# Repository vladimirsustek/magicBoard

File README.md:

<h1>The magicBoard!</h1>

The magicBoard is supposed to multi-purpose embedded device based on the MCU ARM-M7<br> 
STM32F767ZI, namelly on the development board [STM32 Nucleo-144](https://www.st.com/en/evaluation-tools/nucleo-f767zi.html)
equipped with customized<br>shield to extend Nucleo's functionality.

This project has default structure for STM's [STM32CudeIDE](https://www.st.com/en/development-tools/stm32cubeide.html#:~:text=STM32CubeIDE%20is%20an%20advanced%20C,and%20GDB%20for%20the%20debugging.)
. Download this free IDE to build the project.<br><br><br>

<h2>Intended usage is:</h2>
<ol>
  <li>WIFI/Ethernet controlled digital TFT Clock + FM Radio + Thermometer + Pager</li>
  <li>WIFI/Ethernet controlled water-your-plants device for remote/automatic control</li>
  <li>WIFI/Ethener/UART controlled experimental device to generate and process signals</li>
</ol>

<h2>STM32F767ZI Nucleo-144 main features:</h2>

<ol>
  <li>USB FS (VCOM, HID..)</li>
  <li>Ethernet (RJ45)</li>
  <li>8MHz and 32.768kHz XTAL</li>
  <li>Arduino and ZIO connectors - <b>interface for the magicBoard</b></li>
</ol>

<h2>magicBoard shield features:</h2>

For more hardware details see [Schematics](/Docs/magicBoard.pdf)

<ol>
  <li><b>MONO AUDIO IN - analog pre-processing of 3.5mm jack signal</b><ul>
      <li>add offset to an AC audio signal for DC signal for MCU's ADC sampling</li>
      <li>amplify the audio signal to use full Rail-to-Rail MCU's ADC sampling</li>
	  <li>allow AC audio as well as DC testing signal processing ('no AC coupling')</li>
	  <li>used OPAMP LMV358 as a weighted sum amplifier</li>
  </ul></li>
  <li><b>STEREO AUDIO OUT - analog amplification for a speaker</b><ul>
      <li>buffer/amplify MCU's DAC output to provide enough power for a speaker</li>
	  <li>allow 'no amplifier' or 'no AC coupling' mode to generate DC test waveforms</li>
	  <li>selectable maximal output voltage (3V3, 5V, VIN)</li>
	  <li>used OPAMP LM386 as an audio aplifier</li>
  </ul></li>
  <li><b>LCD - development and usage information display TFT 3.5''</b><ul>
      <li>Display text in fonts up to '100' for alarm clock usage</li>
	  <li>Display text of smaller formats for dense information</li>
	  <li>Parallel 8+5 communication bus</li>
  </ul></li>
  <li><b>2x PWM - power driver for DC-brush-motor</b><ul>
      <li>H-Bridge operation mode</li>
	  <li>Thermal and current shutdown</li>
	  <li>Experimental signal generation</li>
	  <li>selectable maximal output voltage (3V3, 5V, VIN)</li>
	  <li>used DRV8220 as a PWM driver</li>
	  <li>direct duty cycle control + sleep</li>
  </ul></li>
  <li><b>2x NRF24L01+ module interface</b><ul>
      <li>For low-power sensor interfacing</li>
	  <li>2x for on-board development (controlled by one host)</li>
	  <li>Power supply rail controlled by P-MOSFET</li>
	  <li>2-row female pin header (4x2)</li>
	  <li>SPI communication bus + IRQ, CE</li>
  </ul></li>
    <li><b>ESP8266-01 module interface</b><ul>
      <li>For WIFI applications </li>
	  <li>Power supply rail controlled by P-MOSFET</li>
	  <li>2-row female pin header (4x2)<\li>
	  <li>UART communication bus + IO, RST</li>
  </ul></li>
   <li><b>RDA5807M module interface</b><ul>
      <li>For FM Radio applications + RDS </li>
	  <li>Power supply rail controlled by P-MOSFET</li>
	  <li>male pin header (4x1)<\li>
	  <li>connection to AUDIO IN and AUDIO OUT possible</li>
	  <li>I2C communication bus</li>
  </ul></li>
    <li><b>25AA1024 EEPROM</b><ul>
      <li>Non-volatile memory to save MCU's FLASH</li>
	  <li>SPI communication bus</li>
  </ul></li>
      <li><b>4x Button</b><ul>
      <li>to emaluate all 4 keyboard arrows or the gaming W-A-S-D navigation</li>
  </ul></li>
  <li><b>2x LED</b><ul>
      <li>white and green for general purposes</li>
  </ul></li>
  <li><b>Power supply options</b><ul>
      <li>To use Nucleo-144 3V3, 5V or external voltages</li>
  </ul></li>
</ol>

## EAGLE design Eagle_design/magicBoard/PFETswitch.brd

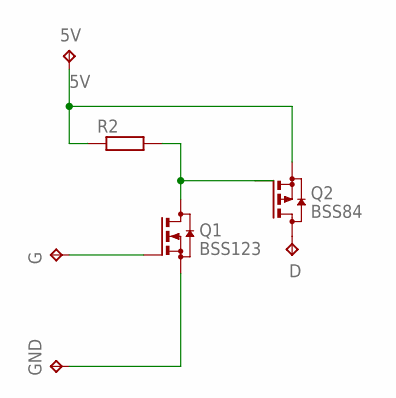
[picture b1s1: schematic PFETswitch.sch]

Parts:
5V: TPTP09SQ; TP09SQ
D: TPTP09SQ; TP09SQ
G: TPTP09SQ; TP09SQ
GND: TPTP09SQ; TP09SQ
Q1: BSS123; SOT23
Q2: BSS84; SOT23
R2: R-EU_R0603; R0603

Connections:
5V: 5V.TP, Q2.2 (S), R2.1
unnamed: G.TP, Q1.1 (G)
unnamed: Q1.3 (D), Q2.1 (G), R2.2
unnamed: GND.TP, Q1.2 (S)
unnamed: D.TP, Q2.3 (D)

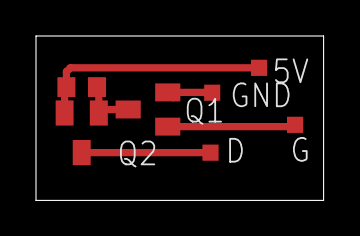
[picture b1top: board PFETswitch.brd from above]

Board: 2 copper layers, 16.0 x 9.1 mm, 7 parts (0 on the bottom side), 5 nets.

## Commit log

2022-11-26 Finished v1
2022-11-28 Final pin INIT before review
2022-12-18 HW-BringUp : NRFs 1/2
2022-12-18 HW-BringUp : NRFs OK
2022-12-18 Adding docs
2022-12-18 ESP8266 and 25AA1024 BringUp: OK
2022-12-21 RDA5807M BringUp: OK
2022-12-21 Corrected gitingore
2022-12-21 LED1-LED2 HW-BringUp - OK
2022-12-21 TFT Display HW-BringUp: OK
2022-12-24 AO_PWR BringUp: OK
2022-12-28 cli_du BringUp: OK
2022-12-29 cmd_dispatcher and cli fully operational (DMA)
2022-12-29 Introduced nvm_app layer, ESP wifi OK
2023-01-14 Drivers clean-up
2023-01-14 Code cleaup - NVM
2023-01-14 NVM system states cleanup finished
2023-01-16 Functional Magneto120
2023-01-25 Functional magneto
2023-01-26 Functional magneto 100/40, user diplay layout
2023-01-26 Calibri16 added
2023-01-30 Informal/navigation changes readme
2023-01-31 Minor fixes for better readability
2023-01-31 Readme update
2023-01-31 Readme minor fixes
2023-01-31 Minor README fixes
2023-01-31 Added full PCB design
2023-03-03 Fixed linker bugs and paths, starting optimizing display
2023-03-08 Added ADC measurements
2023-03-11 Corrected includes, print_magneto.c, tft.c, esp8266_http_data.c
2023-03-11 Minor main fixes
2023-03-11 Functional, temporary RTOS receiving the sensor (unstable sensor)
2023-03-12 Fixed nrf-ports
2023-03-12 Corrected paths
2023-03-12 Wireless VDDA, 512*8B task STACK influenced HardFault (orig 128*8)
2023-03-12 Optimized tasks, time malfuction, not fully "synced"
2023-03-12 RTC hard coded solution
2023-03-26 Functional WIFI clock
2023-05-12 Functional state, missing LAN
2023-05-20 Added Nucleo-144 schematic
